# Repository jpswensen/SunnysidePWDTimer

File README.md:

# SunnysidePWDTimer

This is an early prototype of a simple 4-lane pinewood derby timer created using the popular Internet of Things (IOT) device ESP8266, 
some cheap IR line detectors sensors, and a limit switch for the starting gate.

Parts List
================
* 1) Wemos D1 Mini - $7.49 (https://www.amazon.com/HiLetgo-NodeMcu-Development-ESP8266-Compatiable/dp/B01IXBWH9Y)
* 2) OSOYOO 10PCS IR Infrared Obstacle Avoidance Sensor Module for Arduino Smart Car Robot - $9.99 for a 10 pack (https://www.amazon.com/gp/product/B01I57HIJ0)
* 3) Limit switch for gate sensor (must have normally closed terminals) - $8.89 for a 20 pack (https://www.amazon.com/Gikfun-Micro-Switch-Arduino-EK1713/dp/B015W8S8NA)
* 4) Some 3D printed parts for mounting the sensor to the lanes and the limit switch

Details
================
The project contains both a cross-platform QT5 project for the PC side and Arduino code forht Wemos D1 Mini. They communicate through the
serial port built into the Wemos D1 Mini carrier board for the ESP8266 IOT mainboard. Here is a list of pin configurations:

 * D7 - Start gate limit switch
 * D1 - Lane A
 * D2 - Lane B
 * D5 - Lane C
 * D6 - Lane D

I plan on uploading the Solidworks and STL files for our particular track so that it would be easy for others to modify for their track.
This software is clearly not as fully functional as the Grand Prix Race Manager (TM) software, but it is free and the timer costs about $20-25
if you can get a bit of donated 3D printing from a parent or friend of the pack. I would welcome collaborators to make the software really fully
functional (e.g. support dens/groups/subgroups, printing certificates, etc.) I was actually really surprised when our pack was buying a new track
that was around $1,000 and even a cheap timer was over $219. The timer sold by the track manufacturer was really nice, but cost another $600
beyond the cost of the track.

Let me know if you have any questions and would like to collaborate.

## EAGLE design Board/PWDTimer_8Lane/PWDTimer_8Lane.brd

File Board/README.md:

# SunnysidePWDTimer

This is an initial schematic and board design for an 8-lane pinewood
derby timer.

THIS HAS NOT BEEN TESTED YET. THE CODE AND GUI INCLUDED IN THIS
PROJECT WERE BASED ON A 4-LANE HAND SOLDERED BOARD I MADE. THIS BOARD
IS BASED ON THAT AND SHOULD WORK FOR UP TO 8 LANES, BUT THE ARDUINO
CODE AND GUI CODE HAVE NOT BEEN UPDATED TO WORK WITH THIS DESIGN YET.

Parts List
================
* 1) Wemos D1 Mini - $7.49 (https://www.amazon.com/HiLetgo-NodeMcu-Development-ESP8266-Compatiable/dp/B01IXBWH9Y)
* 2) OSOYOO 10PCS IR Infrared Obstacle Avoidance Sensor Module for Arduino Smart Car Robot - $9.99 for a 10 pack (https://www.amazon.com/gp/product/B01I57HIJ0)
* 3) Limit switch for gate sensor (must have normally closed terminals) - $8.89 for a 20 pack (https://www.amazon.com/Gikfun-Micro-Switch-Arduino-EK1713/dp/B015W8S8NA)
* 4) Some 3D printed parts for mounting the sensor to the lanes and
the limit switch
* 5) See the file SunnysideTimersDigikey.csv for the rest of the
connector, pins, etc from Digikey

In total, I think this time would cost you about $80 to make an 8-lane
timer. If multiple people went together, and it was made in bulk, that
cost could probably be half that much (circuit boards are more
expensive in lower quantity and the cabling is expensive in short lengths). I also chose nice Molex Minifit Jr
connectors which end up being kindof pricy.

Details
================
Here is a description of the files

* SunnysideTimerV1.pro - The project file for Eagle PCB
* SunnysideTimerV1.sch - The schematic file for Eagle PCB
* SunnysideTimerV1.brd - The board file for Eagle PCB

The easiest way to get these made is to go to https://oshpark.com/ and
just upload the .brd file. They do all the processing and the price
comes out at around $30 for 3 boards. Not a bad price for a 14 day turnaround.

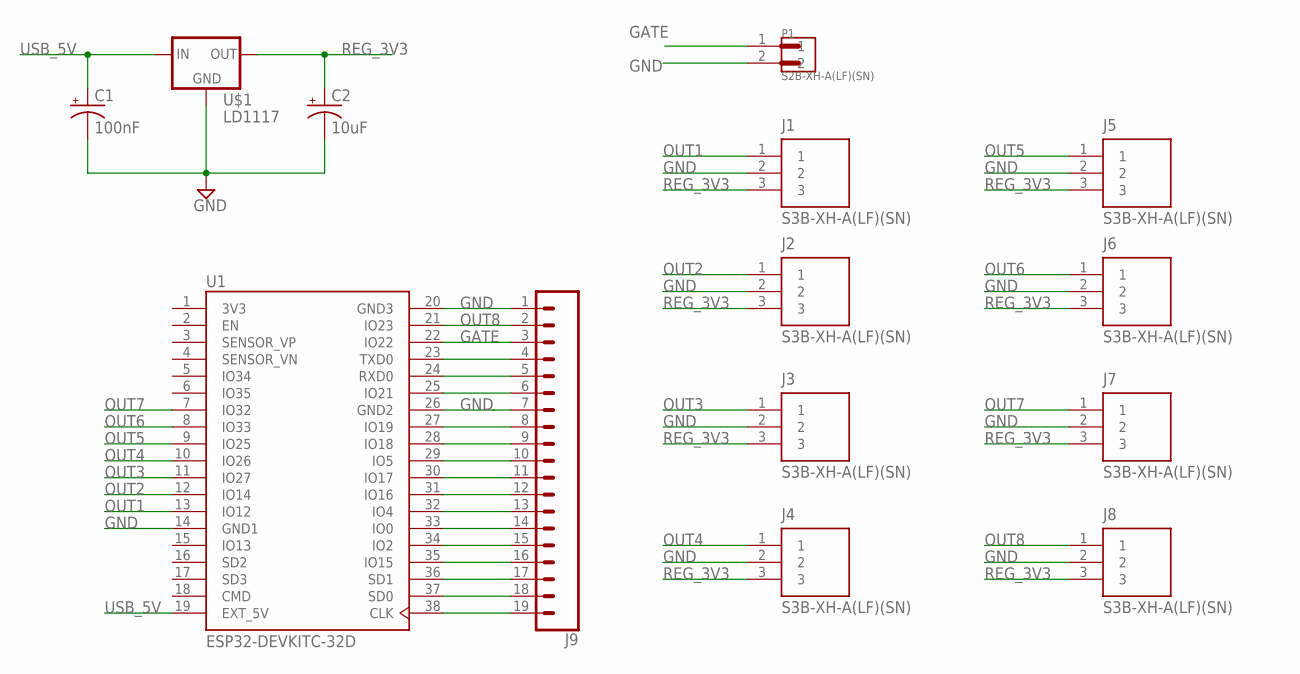
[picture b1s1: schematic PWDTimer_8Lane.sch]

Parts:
C1: 100nF; CPOL-RADIAL-2.5MM-5MM
C2: 10uF; CPOL-RADIAL-2.5MM-5MM
J1, J2, J3, J4, J5, J6, J7, J8: S3B-XH-A(LF)(SN); JST_S3B-XH-A(LF)(SN)
J9: CONN_191X19_NO_SILK; 1X19_NO_SILK
P1: S2B-XH-A(LF)(SN); JST_S2B-XH-A(LF)(SN)
U1: ESP32-DEVKITC-32D; MODULE_ESP32-DEVKITC-32D
U$1: LD1117; TO220

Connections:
3V3: U1.1 (3V3)
GATE: J9.3, P1.1, U1.22 (IO22)
GND: C1.2 (-), C2.2 (-), J1.2, J2.2, J3.2, J4.2, J5.2, J6.2, J7.2, J8.2, J9.1, J9.7, P1.2, U1.14 (GND1), U1.20 (GND3), U1.26 (GND2), U$1.1 (GND)
unnamed: J9.4, U1.23 (TXD0)
unnamed: J9.5, U1.24 (RXD0)
unnamed: J9.6, U1.25 (IO21)
unnamed: J9.8, U1.27 (IO19)
unnamed: J9.9, U1.28 (IO18)
unnamed: J9.10, U1.29 (IO5)
unnamed: J9.11, U1.30 (IO17)
unnamed: J9.12, U1.31 (IO16)
unnamed: J9.13, U1.32 (IO4)
unnamed: J9.14, U1.33 (IO0)
unnamed: J9.15, U1.34 (IO2)
unnamed: J9.16, U1.35 (IO15)
unnamed: J9.17, U1.36 (SD1)
unnamed: J9.18, U1.37 (SD0)
unnamed: J9.19, U1.38 (CLK)
OUT1: J1.1, U1.13 (IO12)
OUT2: J2.1, U1.12 (IO14)
OUT3: J3.1, U1.11 (IO27)
OUT4: J4.1, U1.10 (IO26)
OUT5: J5.1, U1.9 (IO25)
OUT6: J6.1, U1.8 (IO33)
OUT7: J7.1, U1.7 (IO32)
OUT8: J8.1, J9.2, U1.21 (IO23)
REG_3V3: C2.1 (+), J1.3, J2.3, J3.3, J4.3, J5.3, J6.3, J7.3, J8.3, U$1.2 (OUT)
USB_5V: C1.1 (+), U1.19 (EXT_5V), U$1.3 (IN)

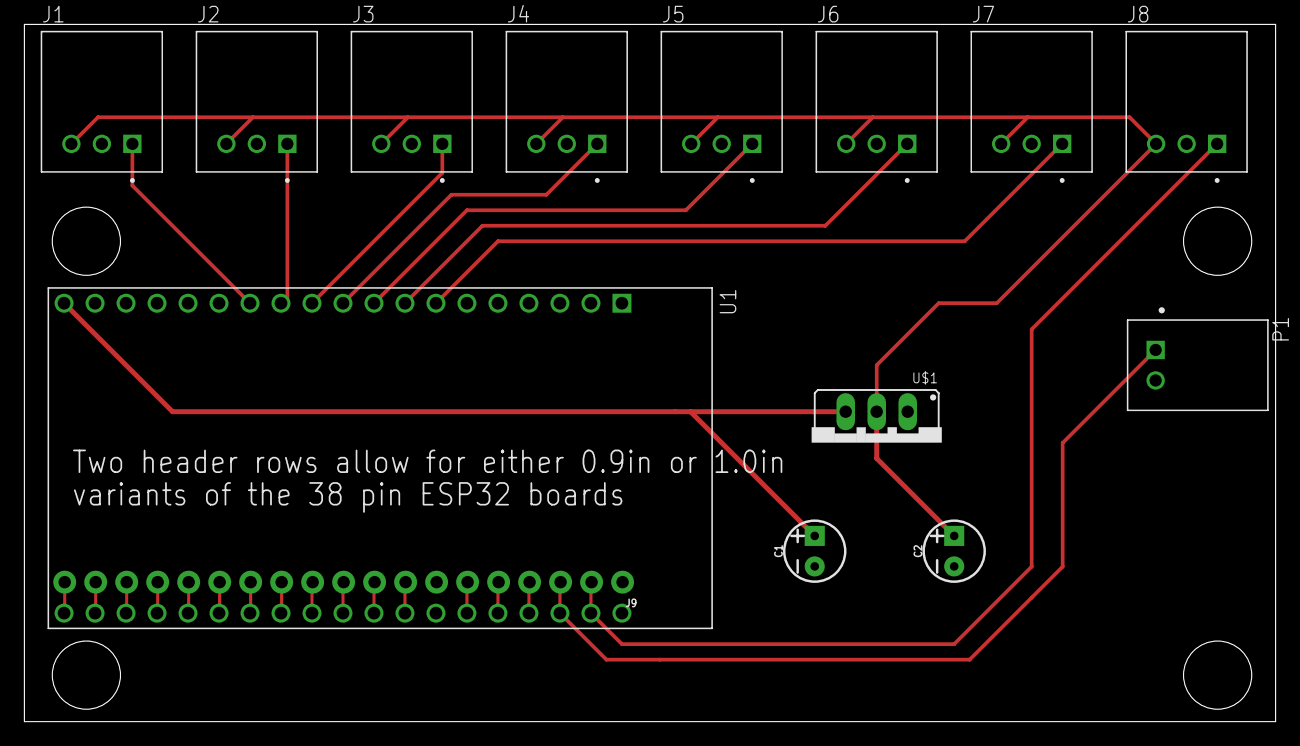
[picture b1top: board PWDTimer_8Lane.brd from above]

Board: 2 copper layers, 102.5 x 57.1 mm, 14 parts (0 on the bottom side), 27 nets.

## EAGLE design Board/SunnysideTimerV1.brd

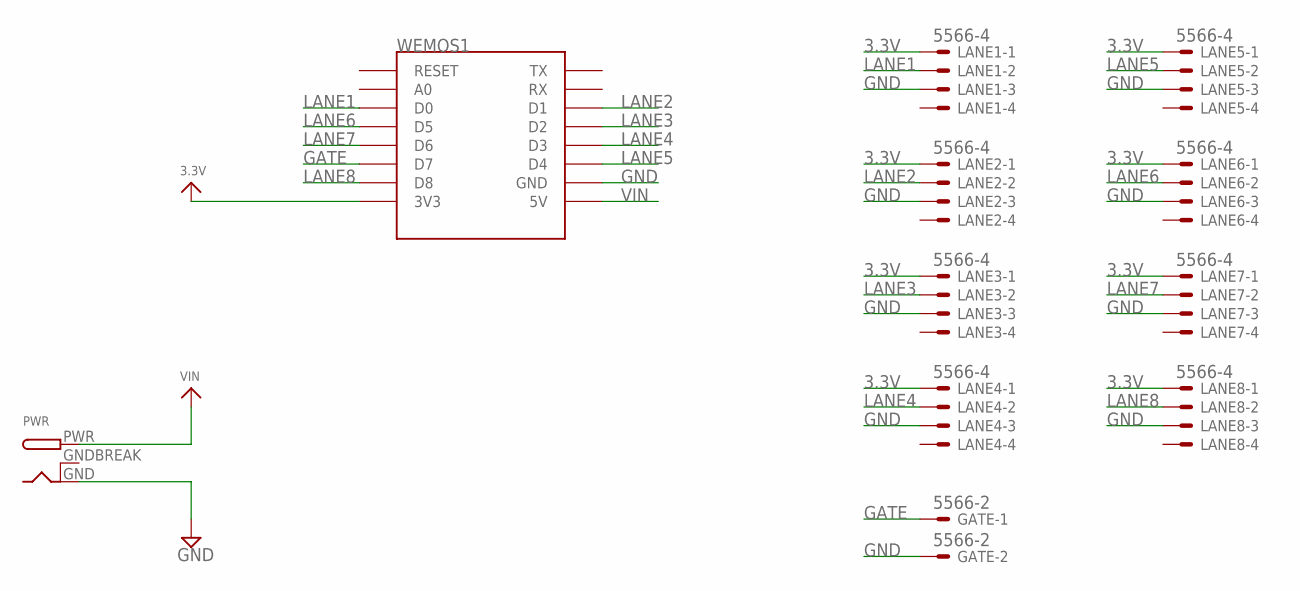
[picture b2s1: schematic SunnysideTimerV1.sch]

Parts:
GATE: 5566-2
LANE1, LANE2, LANE3, LANE4, LANE5, LANE6, LANE7, LANE8: 5566-4
PWR: DCBARRELPTH; DCJACK_2MM_PTH
WEMOS1: WEMOS-D1-MINI

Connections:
3.3V: LANE1.1, LANE2.1, LANE3.1, LANE4.1, LANE5.1, LANE6.1, LANE7.1, LANE8.1, WEMOS1.3V3
GATE: GATE.1, WEMOS1.D7
GND: GATE.2, LANE1.3, LANE2.3, LANE3.3, LANE4.3, LANE5.3, LANE6.3, LANE7.3, LANE8.3, PWR.GND, WEMOS1.GND
GNDBREAK: PWR.GNDBREAK
LANE1: LANE1.2, WEMOS1.D0
LANE2: LANE2.2, WEMOS1.D1
LANE3: LANE3.2, WEMOS1.D2
LANE4: LANE4.2, WEMOS1.D3
LANE5: LANE5.2, WEMOS1.D4
LANE6: LANE6.2, WEMOS1.D5
LANE7: LANE7.2, WEMOS1.D6
LANE8: LANE8.2, WEMOS1.D8
VIN: PWR.PWR, WEMOS1.5V

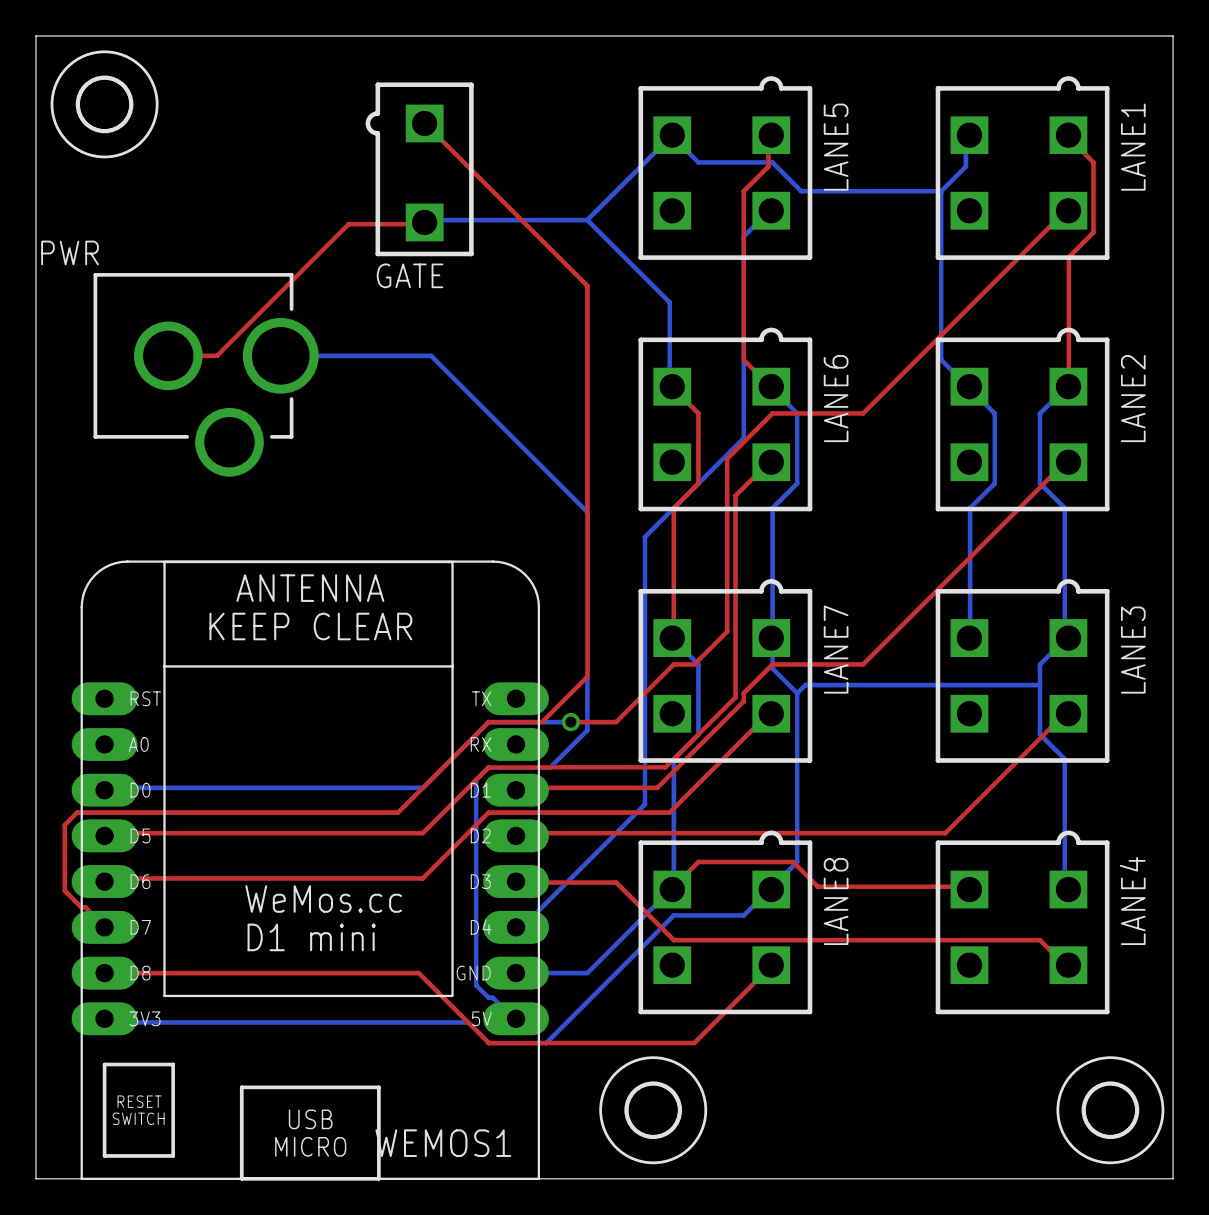
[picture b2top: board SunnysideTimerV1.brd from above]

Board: 2 copper layers, 63.2 x 63.5 mm, 14 parts (0 on the bottom side), 12 nets.

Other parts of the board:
U$3, U$4, U$5: 2,8

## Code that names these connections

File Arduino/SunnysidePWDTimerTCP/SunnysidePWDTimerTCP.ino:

/*
   Copyright (c) 2017, John Swensen
   All rights reserved.

   Redistribution and use in source and binary forms, with or without modification,
   are permitted provided that the following conditions are met:

 * * Redistributions of source code must retain the above copyright notice, this
     list of conditions and the following disclaimer.

 * * Redistributions in binary form must reproduce the above copyright notice, this
     list of conditions and the following disclaimer in the documentation and/or
     other materials provided with the distribution.

   THIS SOFTWARE IS PROVIDED BY THE COPYRIGHT HOLDERS AND CONTRIBUTORS "AS IS" AND
   ANY EXPRESS OR IMPLIED WARRANTIES, INCLUDING, BUT NOT LIMITED TO, THE IMPLIED
   WARRANTIES OF MERCHANTABILITY AND FITNESS FOR A PARTICULAR PURPOSE ARE
   DISCLAIMED. IN NO EVENT SHALL THE COPYRIGHT HOLDER OR CONTRIBUTORS BE LIABLE FOR
   ANY DIRECT, INDIRECT, INCIDENTAL, SPECIAL, EXEMPLARY, OR CONSEQUENTIAL DAMAGES
   (INCLUDING, BUT NOT LIMITED TO, PROCUREMENT OF SUBSTITUTE GOODS OR SERVICES;
   LOSS OF USE, DATA, OR PROFITS; OR BUSINESS INTERRUPTION) HOWEVER CAUSED AND ON
   ANY THEORY OF LIABILITY, WHETHER IN CONTRACT, STRICT LIABILITY, OR TORT
   (INCLUDING NEGLIGENCE OR OTHERWISE) ARISING IN ANY WAY OUT OF THE USE OF THIS
   SOFTWARE, EVEN IF ADVISED OF THE POSSIBILITY OF SUCH DAMAGE.
*/

/* 
  This version of the timer firmware creates a WiFi access point and provides a TCP socket on it.
  This can still be run using the standard serial interface or can be connected to as an access point.
  NOTE: The reason for extending this to a WIFI solution was so that the computer/projector do not
        have to be near the finish line of the race. You will still need to run power to the finish line,
        but you won't need a long USB cable and monitor cable to have a better computer/projector location.
*/

#define USE_US_TIMER 1

#include <ESP8266WiFi.h>
#include <WiFiClient.h>

#include <algorithm>

#define LANE1_PIN D0
#define LANE2_PIN D1
#define LANE3_PIN D2
#define LANE4_PIN D3
#define LANE5_PIN D4
#define LANE6_PIN D5
#define LANE7_PIN D6
#define LANE8_PIN D8

#define STARTGATE_PIN D7



// Enums for maintaining the race and messaging information 
typedef enum RecvMessageEnum {
  UNDEFINED_MSG = 0,
  RESET_MSG
} RecvMessage_t;


typedef enum TimerStateEnum {
  UNDEFINED = 0,
  RESET,
  SET,
  IN_RACE,
  FINISHED
} TimerState_t;


// Variables for determining the state of the race and car times
#define NUM_TIMERS 8
TimerState_t state = RESET;
long startTime = 0;
long endTime[NUM_TIMERS] = {0, 0, 0, 0, 0, 0, 0, 0};


// Variables for configuring the communications
#define SERIAL_BAUD 115200

#define MAX_SRV_CLIENTS 1
#define TCP_PORT        8080

const char *ssid = "PWDTIMER";
const char *password = "PWDTIMER";
WiFiServer server(TCP_PORT);
WiFiClient serverClients[MAX_SRV_CLIENTS];


/**************************************************************************************************************
 * INTERRUPT HANDLING
 **************************************************************************************************************/

// Declare and ISR handler that can deal with any of the lanes
void laneInterrupt(int num)
{
  if (endTime[num] == 0)
  {
    //Serial.println("Lane1 interrupt");
    endTime[num] = micros();

    bool is_finished = true;
    for (int i = 0 ; i < NUM_TIMERS ; i++)
    {
      is_finished &= (endTime[i] != 0);
    }
    state = is_finished ? FINISHED : IN_RACE;    
  }
}

// Create a templated function that uses the ISR number as the template parameter
template<int N>
void laneInterruptISR() {
  laneInterrupt(N);
}

void startGateInterrupt() {
  //Serial.println("Start gate interrupt");
  if (state == SET)
  {
    startTime = micros();
    
    endTime[0] = 0;
    endTime[1] = 0;
    endTime[2] = 0;
    endTime[3] = 0;
    endTime[4] = 0;
    endTime[5] = 0;
    endTime[6] = 0;
    endTime[7] = 0;

    state = IN_RACE;
  }
}
 
void setupInterrupts () {
  // Set up the gate and lane pins as inputs with weak pull-ups
  pinMode(LANE1_PIN, INPUT_PULLUP);
  pinMode(LANE2_PIN, INPUT_PULLUP);
  pinMode(LANE3_PIN, INPUT_PULLUP);
  pinMode(LANE4_PIN, INPUT_PULLUP);
  pinMode(LANE5_PIN, INPUT_PULLUP);
  pinMode(LANE6_PIN, INPUT_PULLUP);
  pinMode(LANE7_PIN, INPUT_PULLUP);
  pinMode(LANE8_PIN, INPUT_PULLUP);
  pinMode(STARTGATE_PIN, INPUT_PULLUP);

  // Attach the interrupts for each of the lanes.
  // NOTE: Here we are using some C++ template magic above to only have to declare the ISR once.
  attachInterrupt(LANE1_PIN, laneInterruptISR<1>, FALLING);
  attachInterrupt(LANE2_PIN, laneInterruptISR<2>, FALLING);
  attachInterrupt(LANE3_PIN, laneInterruptISR<3>, FALLING);
  attachInterrupt(LANE4_PIN, laneInterruptISR<4>, FALLING);
  attachInterrupt(LANE5_PIN, laneInterruptISR<5>, FALLING);
  attachInterrupt(LANE6_PIN, laneInterruptISR<6>, FALLING);
  attachInterrupt(LANE7_PIN, laneInterruptISR<7>, FALLING);
  attachInterrupt(LANE8_PIN, laneInterruptISR<8>, FALLING);

  // Attach the starting gate interrupt
  attachInterrupt(STARTGATE_PIN, startGateInterrupt, FALLING);
}


/**************************************************************************************************************
 * COMMUNICATIONS : TCP (DATA) AND SERIAL (DEBUG)
 **************************************************************************************************************/
void setupCommunications() {
  delay(1000);
  Serial.begin(SERIAL_BAUD);
  Serial.println();

  Serial.print("Setting up soft-AP...");
  boolean result = WiFi.softAP(ssid, password);
  if(result == true)
  {
    IPAddress myIP = WiFi.softAPIP();
    Serial.print("Success!");
    Serial.print("    soft-AP IP address: ");
    Serial.println(myIP);
  }
  else
  {
    Serial.println("Failed to set up soft-AP");
  }

}
    

void setupTCPserver() {  
  server.begin();
  server.setNoDelay(true); 
}

void processTCPserverConnections() {
  uint8_t i;
  if (server.hasClient()){
    for(i = 0; i < MAX_SRV_CLIENTS; i++){
      if (!serverClients[i] || !serverClients[i].connected()){
        if(serverClients[i]) serverClients[i].stop();
        serverClients[i] = server.available();
        continue;
      }
    }
    //no free spot
    WiFiClient serverClient = server.available();
    serverClient.stop();
  }
}

RecvMessage_t readMessage()
{
  // TODO: Check both the serial and the TCP for a message
  
  // Check whether a reset command has been sent via serial
  if (Serial.available() >=5)
  {
    String readString;
    while (Serial.available()) {
      char c = Serial.read();  //gets one byte from serial buffer
      readString += c; //makes the string readString
    }

    
    if (readString.equals("RESET"))
    {
      return RESET_MSG;
    }
  }
  
  return UNDEFINED_MSG;
}

void sendMessage(int currentTime)
{
  // Build the message to be sent
  char msgBuffer[512];
  sprintf(msgBuffer, "$%d,%d,%d,%d,%d,%d,%d,%d,%d,%d,%d*", state, startTime, currentTime,
                     endTime[0], endTime[1], endTime[2], endTime[3],
                     endTime[4], endTime[5], endTime[6], endTime[7]);

  // Send the message over serial
  Serial.println(msgBuffer);

  // Send the message over TCP (if connected)
  if (serverClients[0] && serverClients[0].connected()){
    serverClients[0].println(msgBuffer);
  }
}

/**************************************************************************************************************
 * VARIOUS OTHER FUNCTIONS
 **************************************************************************************************************/
void resetRace() {
  state = RESET;
  startTime = -1;
  for (int i = 0 ; i < NUM_TIMERS ; i++) {
    endTime[i] = 0; 
  }
}


/**************************************************************************************************************
 * SETUP AND LOOP
 **************************************************************************************************************/
void setup() {
  delay(1000);
  setupCommunications();

  setupTCPserver();

  setupInterrupts();
}

void loop() {

  // Process TCP connects and disconnects
  processTCPserverConnections();

  // Read in messages from either serial or TCP
  RecvMessage_t msg = readMessage();
  if (msg == RESET_MSG) {
    resetRace();
  }
  

  long currentTime = -1;
  
  switch (state) {
    case RESET:
      startTime = -1;

      if (digitalRead(STARTGATE_PIN) == HIGH)
      {
        state = SET;
      }
      else
      {
        sendMessage(currentTime);
      }
      
      break;

    case SET:
      sendMessage(currentTime);
      break;

    case IN_RACE:
      currentTime = micros();
      sendMessage(currentTime);
      break;

    case FINISHED:
      currentTime = std::max(std::max(std::max(endTime[0], endTime[1]),endTime[2]),endTime[3]);
      sendMessage(currentTime);
      break;
    
  }

  delay(50);
  
}

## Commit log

2017-03-03 Initial commit of the project
2017-03-03 Started to name various UI elements appropriately and get them set up in the MainWindow constructor for easier access once the race schedule portion of the main window is completed.
2017-03-04 Switched to using the serial port (then we can just plug into whatever computer we are using). It also seems to transmit faster. I also think I have all of the logic working for resetting the timer, 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
2017-03-04 Added the Arduino/ESP8266 code to the repository. Now that I switched to serial, this should work with basically any Arduino-compatible microcontroller that has at least 5 pins with interrupt-on-chan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
2017-03-04 Took out all remnants of the UDP code on the microcontroller side of things.
2017-03-04 I almost have the basics of the heats panel completed. There is still no interaction between the heats panel and the single heat panel, but the basics are there.
2017-03-04 Started to implement the add/delete user table
2017-03-04 Added the .DS_Store to the gitignore file
2017-03-05 Finished up the heats panel, load & save from CSV, and participant editor. I need to clean the code up quite a bit, but it is looking OK. I did notice it looks kindof bad on my Mac when not connected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
2017-03-05 Starting to comment a bit, in the case anyone wants to help out.
2017-03-06 Added the printable results view. Various other small fixes. Other than a dialog that allows the selection of the serial port and a little better interaction between the microcontroller and the deskt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
2017-03-06 Updated what is done and what isn't done.
2017-03-07 More updates. I think it is basically ready to go. I still need to write some documentation.
2017-03-13 Various bug fixed for crashes when the serial port isn't open. Added some beginning documentation.
2017-03-14 Added an app icon. Changed the project file to release build.
2017-03-16 .pro modifications from David Gneiting for Windows+MacOS support
2017-03-16 Added a first release for both Windows and MacOS
2017-03-18 Adjusted font sizes. Error proofed the reset button. Auto-resize the results rows.
2017-03-18 Made a few more font size modifications and included David's changes to the UI file. Including second Windows version.
2018-03-15 Updates to documentation and uploaded the V2 of the MacOS version
2018-03-21 Added the initial circuit board design and description to the repository
2018-03-22 Added an updated firmware version that can handle up to 8 lanes and can communicate over a TCP socket (it sets itself up as a WIFI access point)
2022-03-19 Lots of updates, but haven't had the time to organize it and remove the old stuff. This is a halfway step to a much, much better timer. The design has been updated to use an ESP32 instae of the ESP82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
2022-03-19 Beginning to implement the GUI in Python instead of C/C++
2022-03-19 Fixed a bug on serial receive if any garbage characters come in (e.g. from board resetting)
2022-03-19 Change filename
2022-03-19 The comm dialog is now working pretty well. I think I need to add a lot more robustness to checking for loss of communications, but it is working.
2022-03-20 Lots of updates to include the load and save of race files, as well as the rest of functionality for rows
2022-03-20 Added a bunch of code for running pyinstaller to make a single binary. Also added a readme with that command
2022-03-21 Starting to build in the ability to create groups of racers, so that it would be easier for larger packs to create different dens
2022-03-23 Lots of updates to changing how data is stored as a json file, as well as starting the conversion to having groups and racers in the groups instead of just one monolothic racer group.
2022-03-24 The write out to json is now working, as well as the adding and removing of racers in a group
2022-03-24 A few steps forward on the new UI
2022-03-24 Almost completed the switchover from everything being in the main UI file, to having a separate ui file and python file for each tab panel. This should also make it easier to make 'plugins' for futur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
2022-04-01 This seems fairly close to MVP status. I have tested the serial communications thoroughly. Fixed a bug where serial wouldn't start working until Wifi succeeded. Connect and disconnect seems to work. 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

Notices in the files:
parts and their libraries:
SparkFun-Capacitors: Licensing: Creative Commons ShareAlike 4.0 International - https://creativecommons.org/licenses/by-sa/4.0
microbuilder: This work is placed in the public domain, and may be freely used for commercial and non-commercial work with the following conditions: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
